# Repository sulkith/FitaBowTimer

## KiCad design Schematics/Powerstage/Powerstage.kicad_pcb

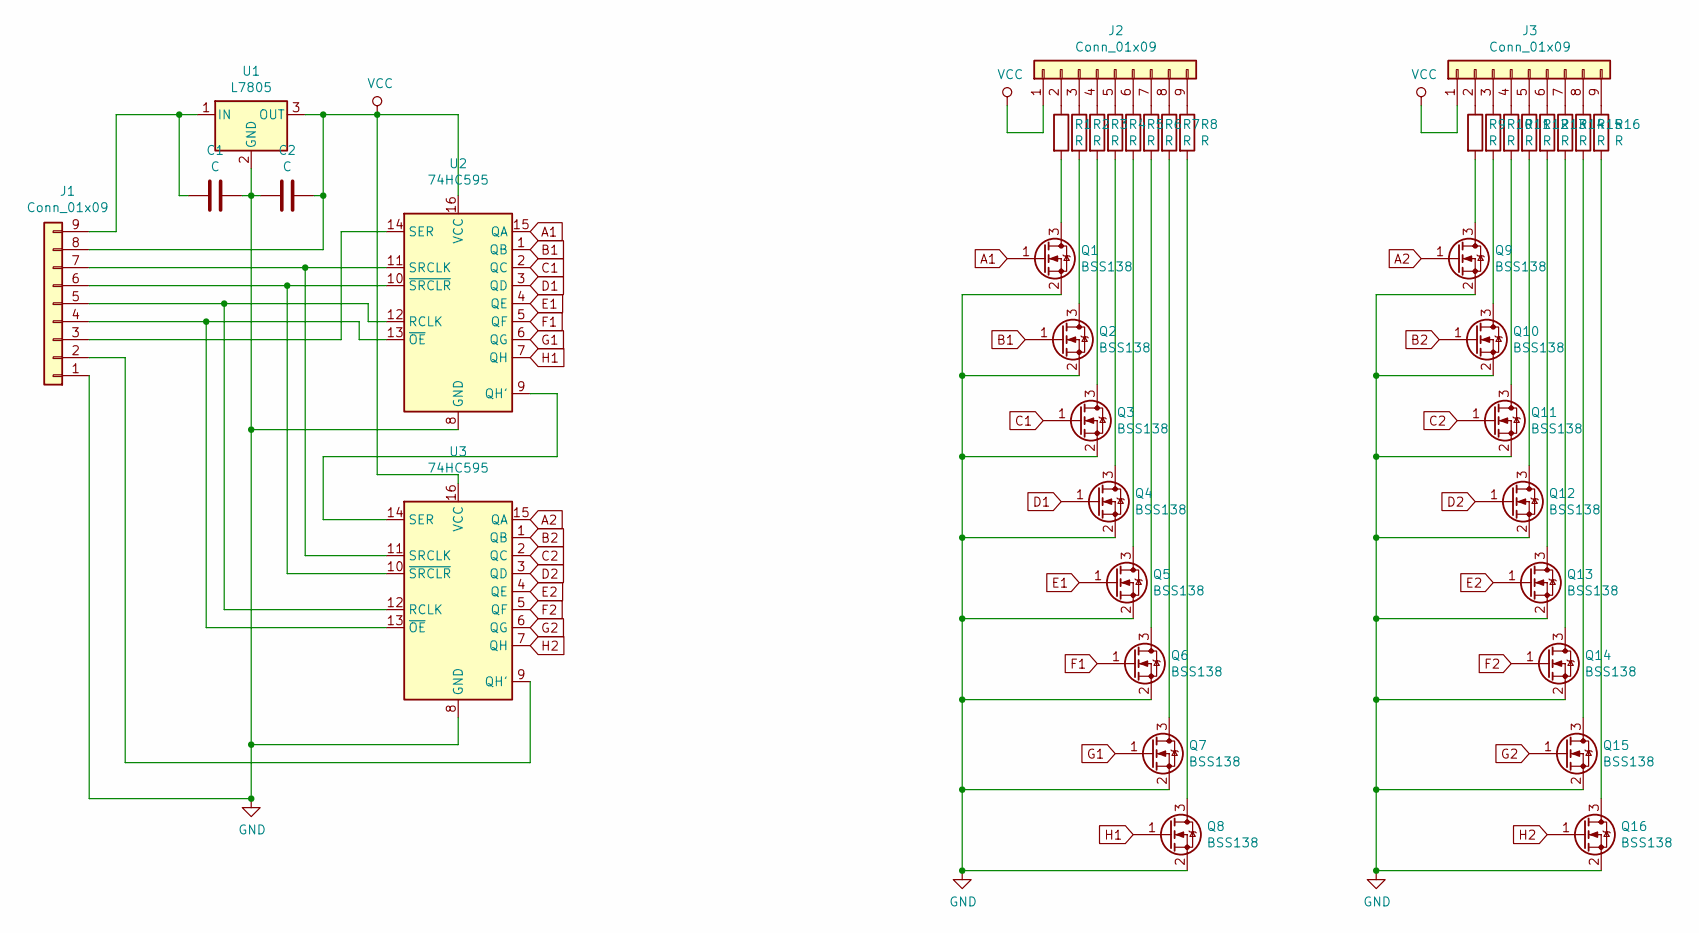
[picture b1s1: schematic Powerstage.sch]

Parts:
C1, C2: C; C_0603_1608Metric
J1, J2, J3: Conn_01x09; PinHeader_1x09_P2.54mm_Vertical
Q1, Q2, Q3, Q4, Q5, Q6, Q7, Q8, Q9, Q10, Q11, Q12, Q13, Q14, Q15, Q16: BSS138; SOT-23
R1, R2, R3, R4, R5, R6, R7, R8, R9, R10, R11, R12, R13, R14, R15, R16: R; R_1206_3216Metric_Pad1.42x1.75mm_HandSolder
U1: L7805; TO-220-3_Vertical
U2, U3: 74HC595; DIP-16_W7.62mm

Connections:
A1: Q1.1 (G), U2.15 (QA)
A2: Q9.1 (G), U3.15 (QA)
B1: Q2.1 (G), U2.1 (QB)
B2: Q10.1 (G), U3.1 (QB)
C1: Q3.1 (G), U2.2 (QC)
C2: Q11.1 (G), U3.2 (QC)
D1: Q4.1 (G), U2.3 (QD)
D2: Q12.1 (G), U3.3 (QD)
E1: Q5.1 (G), U2.4 (QE)
E2: Q13.1 (G), U3.4 (QE)
F1: Q6.1 (G), U2.5 (QF)
F2: Q14.1 (G), U3.5 (QF)
G1: Q7.1 (G), U2.6 (QG)
G2: Q15.1 (G), U3.6 (QG)
GND: C1.1, C2.2, J1.1, Q1.2 (S), Q2.2 (S), Q3.2 (S), Q4.2 (S), Q5.2 (S), Q6.2 (S), Q7.2 (S), Q8.2 (S), Q9.2 (S), Q10.2 (S), Q11.2 (S), Q12.2 (S), Q13.2 (S), Q14.2 (S), Q15.2 (S), Q16.2 (S), U1.2 (GND), U2.8 (GND), U3.8 (GND)
H1: Q8.1 (G), U2.7 (QH)
H2: Q16.1 (G), U3.7 (QH)
unnamed: C1.2, J1.9, U1.1 (IN)
unnamed: J1.2, U3.9 (QH')
unnamed: J1.3, U2.14 (SER)
unnamed: J1.4, U2.13 (~OE), U3.13 (~OE)
unnamed: J1.5, U2.12 (RCLK), U3.12 (RCLK)
unnamed: J1.6, U2.10 (~SRCLR), U3.10 (~SRCLR)
unnamed: J1.7, U2.11 (SRCLK), U3.11 (SRCLK)
unnamed: J2.2, R1.1
unnamed: J2.3, R2.1
unnamed: J2.4, R3.1
unnamed: J2.5, R4.1
unnamed: J2.6, R5.1
unnamed: J2.7, R6.1
unnamed: J2.8, R7.1
unnamed: J2.9, R8.1
unnamed: J3.2, R9.1
unnamed: J3.3, R10.1
unnamed: J3.4, R11.1
unnamed: J3.5, R12.1
unnamed: J3.6, R13.1
unnamed: J3.7, R14.1
unnamed: J3.8, R15.1
unnamed: J3.9, R16.1
unnamed: Q1.3 (D), R1.2
unnamed: Q2.3 (D), R2.2
unnamed: Q3.3 (D), R3.2
unnamed: Q4.3 (D), R4.2
unnamed: Q5.3 (D), R5.2
unnamed: Q6.3 (D), R6.2
unnamed: Q7.3 (D), R7.2
unnamed: Q8.3 (D), R8.2
unnamed: Q9.3 (D), R9.2
unnamed: Q10.3 (D), R10.2
unnamed: Q11.3 (D), R11.2
unnamed: Q12.3 (D), R12.2
unnamed: Q13.3 (D), R13.2
unnamed: Q14.3 (D), R14.2
unnamed: Q15.3 (D), R15.2
unnamed: Q16.3 (D), R16.2
unnamed: U2.9 (QH'), U3.14 (SER)
VCC: C2.1, J1.8, J2.1, J3.1, U1.3 (OUT), U2.16 (VCC), U3.16 (VCC)

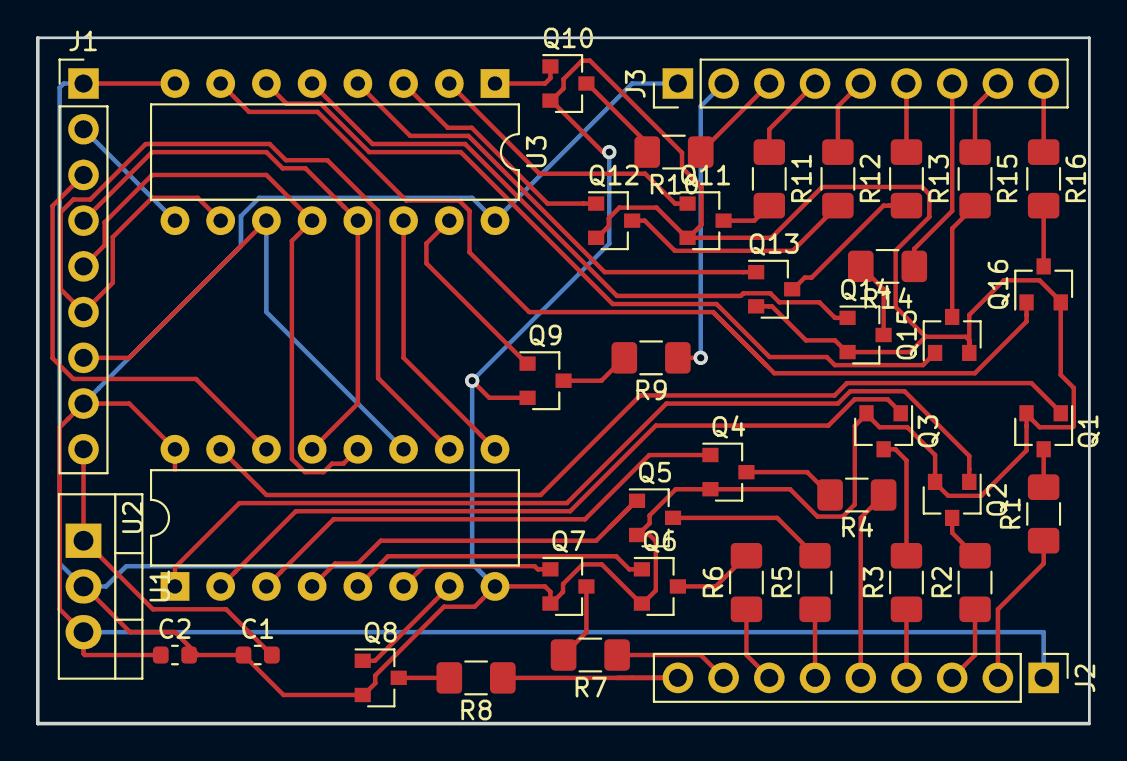
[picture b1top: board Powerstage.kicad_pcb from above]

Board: 2 copper layers, 58.4 x 38.1 mm, 40 parts (0 on the bottom side), 58 nets.

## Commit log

2019-09-30 added Powerstage schematics
